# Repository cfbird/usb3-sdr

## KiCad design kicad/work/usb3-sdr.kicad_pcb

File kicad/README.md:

# usb3-sdr KiCad 9 project (Rev A0, generated)

Open `usb3-sdr.kicad_pro` in KiCad 9. Sheets: Power, RF front end, ADC and clock, USB 3 bridge, FPGA.

**Generated, not hand-drawn:** `gen/build.py` builds every sheet from `gen/design.py` (pin maps checked against
datasheets) and places a net label exactly on each pin end. Connectivity is exact; the visual layout is a packed
netlist style, not tidied. If you edit in KiCad, stop regenerating (or move the edits into design.py).

```
cd gen && python3 build.py && python3 verify.py && python3 check_lpf.py   # regenerate + check
kicad-cli sch erc --severity-all ../usb3-sdr.kicad_sch
```

## Verification status
| Check | Result |
|---|---|
| `gen/verify.py`: KiCad-exported netlist vs design.py | **203/203 nets identical** (no missing, merged or extra nets), 226 components |
| `gen/check_lpf.py`: gateware LPF → KiCad net → far-end **datasheet pin name** (through series resistors) | **71/71 signals land on the right pin**. Independent of design.py |
| ECP5 ball data: Lattice FPGA-SC-02033 CSV vs prjtrellis-db | Same 197 I/O balls, 0 bank mismatches, 0 clock-function mismatches. Pin names in the symbol are the official Lattice names |
| ERC | **2 violations, both expected**: J1 SSRX± "input not driven" (the host drives them through the cable) |
| Symbols vs datasheets | FT601Q (all 76 pins + EP), USB3 Micro-B, TPS62A02A, TLV75525, TPS7A20 DBV, TPS22918 (= TPS22917DBV pinout), W25Q128JVS, PHA-13LN, 74LVC1G17, G6K-2 vs HFD4/5-SR wiring |
| Footprints vs datasheets | FT601 QFN-76 EP 5.81×6.31 (DS Fig 8.3), AD9649 CP-32-11 EP 3.50 sq, BGA-256 14×14 0.8 mm, ADT4-6T+ CD637 |

## Open items
1. ~~ECP5 power/config unit~~ **Done** from Lattice FPGA-SC-02033 (`gen/ecp5_bg256.json`, extracted from the CSV).
   Configuration follows the Lattice ECP5 Versa board (FPGA-EB-02021 Fig. 12): CFG[2:0] = 010 (Master SPI) via 1k,
   10k pull-ups on PROGRAMN/INITN/DONE, 50 Ω series CCLK at the FPGA, JTAG powered from VCCIO8 (3.3 V).
   The 4.7k TCK pull-down is common Lattice practice, **not** taken from the Versa sheet.
2. J1 footprint is the stock Connfly DS1104-01, but the BOM lists Amphenol GSB343133HR. Pick one and match them.
3. GDT footprint is a 1812 placeholder until a GDT part is chosen.
4. FT601 data/control ball assignment follows the gateware LPF pool and is provisional; reorder at layout.

# PCB (stage 1: setup, placement, fan-out; not routed)
`gen/pcb_build.py` writes `usb3-sdr.kicad_pcb` from the exported netlist (footprints keep their symbol links, so
KiCad's *Update PCB from Schematic* works). It regenerates the placement from scratch, so after hand edits start, stop running it.

| Item | Setting |
|---|---|
| Board | 100 × 60 mm, 4 × M2.5 holes, 1.6 mm |
| Stackup | JLC04161H-7628: 35 µm / 0.2104 mm 7628 (εr 4.4) / 15 µm / 1.065 mm core / 15 µm / 0.2104 mm / 35 µm |
| Planes | In1 = solid GND. In2 = 1V1 under the BGA, 1V8_A under the ADC, 3V3_D across the digital half |
| Net classes | RF50 0.35 mm (confirm in the JLC calculator), USB90 diff 0.26 / 0.15, LVDS100 diff 0.20 / 0.15, PWR 0.4 mm, default 0.15 / 0.127 |
| Vias | 0.2 mm drill / 0.45 mm pad (JLC multilayer minimum, no surcharge) |
| BGA fan-out | 156 dog-bone vias: every power/GND ball, and signal balls in rings ≥ 2. Rings 0-1 escape on F.Cu between balls (needs ~0.1 mm neck-down) |

Checks (`kicad-cli pcb drc --schematic-parity`): **0 parity issues** (227 footprints = netlist, + 4 board-only holes).
Errors: only the 10 SMA edge-launch pads meeting Edge.Cuts (inherent to edge launch). Expected while unrouted: 499
unconnected, 112 dangling fan-out vias, 1V8_A plane isolated. Silkscreen overlap warnings are cosmetic (packed reference designators).

## PCB open items
1. **RF chain needs hand placement** in a straight line (SMA → GDT/clamp → K1/pad → LPF1 → notch → K2/LNA → LPF2 → T1 → ADC)
   with 50 Ω lines and the shield-can outlines. The generator only clusters it.
2. SMA edge position: set at the F.Fab flange line (+2.54 mm). **Check against the Amphenol 132289 drawing.**
3. FPGA 100 nF decoupling is on top around the BGA; moving it under the BGA (B.Cu, between vias) is better.
4. FT601 data balls: reorder to match the FT601 pin order at routing, then update the LPF + design.py and rerun verify/check_lpf.
5. 2V5 and 1V8_D BGA vias (VCCAUX, VCCIO7) need B.Cu feeds; the In2 split only covers 1V1 / 3V3_D / 1V8_A.

# PCB stage 2: scripted critical layout (gen/rf_layout.py), ready for DeepPCB
`gen/make_all.sh` runs everything: schematic → verify → check_lpf → ERC → netlist → PCB → DRC.

**RF chain**, a serpentine in the left third of the board (rows at y = 13 / 30 / 41 mm):
- Row A (→): SMA → GDT (Bourns 2038) → BAV99 clamp → K1 (bypass on NC above, 20 dB π-pad on NO below) → LPF1 → FM notch.
- Row B (←): K2 (bypass on NC below, LNA loop on NO above: DC block → PHA-13LN+ → choke/DC block → 3 dB pad) → LPF2.
- Row C (→): ADT4-6T+ → 200 Ω termination → 33 Ω → 10 pF kickback caps → AD9649 VIN±.
- Series parts sit in line, tank caps directly above their inductors, every shunt part has its own GND via to In1.
  Relays are rotated so COM3/COM6 sit in line with the row. All of it is locked.
**USB3 SuperSpeed**: FT601 → J1, one vertical jog per line (topmost line first, so nothing crosses), TX AC caps
on the lines, 0.2 mm width beside the 0.4 mm-pitch QFN. Locked.

Status: DRC errors only the inherent SMA edge items; schematic parity 0; every scripted net complete; 479 airwires left.
In1/In2 are marked as power layers, so signals stay on F.Cu/B.Cu. USB 2 pair renamed USB_D_P/N so diff-pair detection works.

**DeepPCB**: upload `deeppcb/usb3-sdr_for_deeppcb.zip` (or the two files) at app.deeppcb.ai (the KiCad plugin needs KiCad 10).
Check on return: (1) locked RF/USB tracks unchanged, (2) nothing routed on In1/In2, (3) USB90/LVDS100 pairs coupled,
(4) rerun `kicad-cli pcb drc --schematic-parity`. Their docs don't say whether locked tracks are honoured, so
diff the returned board against this one before accepting.

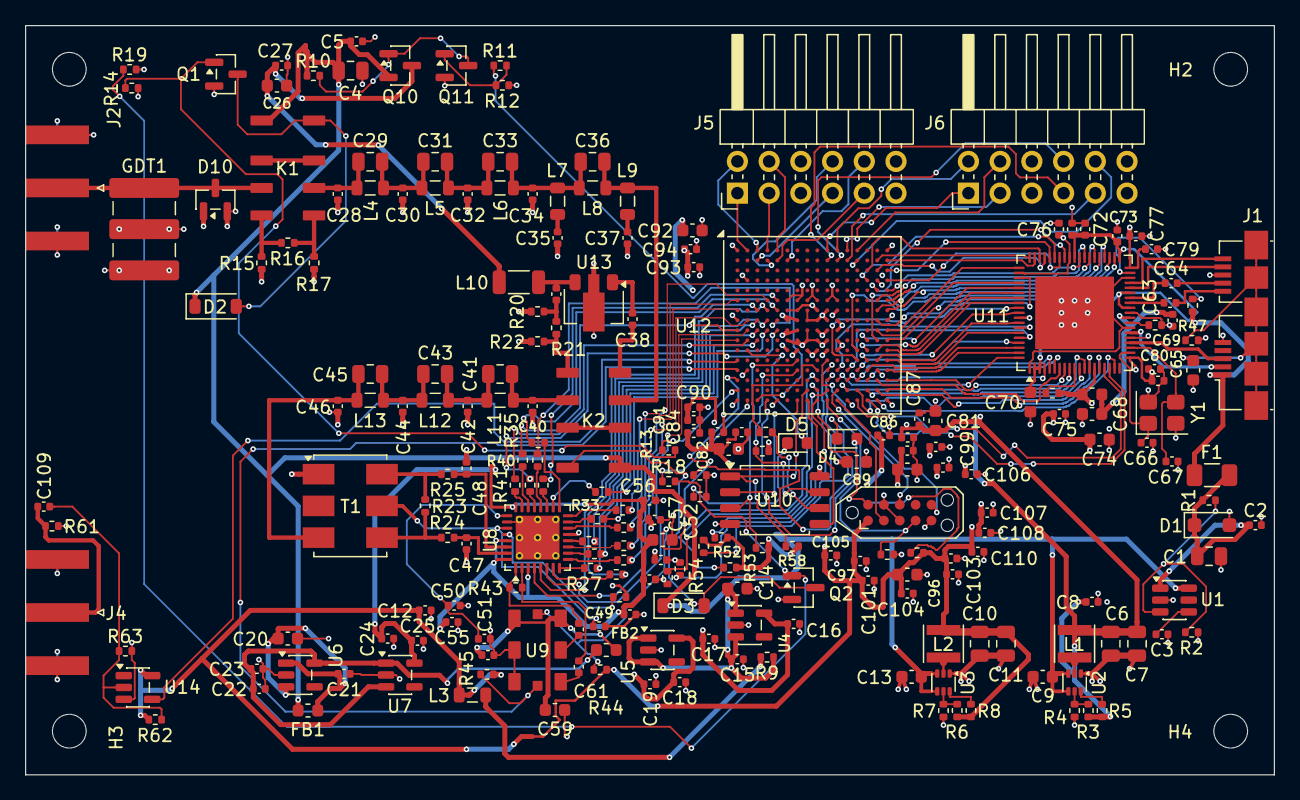
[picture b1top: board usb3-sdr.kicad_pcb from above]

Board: 4 copper layers, 100.0 x 60.0 mm, 231 parts (0 on the bottom side), 203 nets.

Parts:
C1, C4, C6, C7, C10, C11: 22u; C_0805_2012Metric
C2, C5, C8, C12, C17, C19, C21, C23, C25, C27, C38, C39, C49, C51, C53, C54, C55, C56, C58, C60, C61, C62, C63, C64, C69, C71, C72, C73, C75, C76, C77, C78, C79, C80, C83, C84, C85, C86, C87, C88, C90, C91, C93, C94, C97, C98, C99, C100, C101, C102, C103, C104, C105, C106, C107, C108, C109, C110: 100n; C_0402_1005Metric
C3: 1n; C_0402_1005Metric
C9, C13, C14, C20, C26, C52, C59, C74, C81, C82, C89, C92, C95, C96: 10u; C_0603_1608Metric
C15, C16, C18, C22, C24, C50, C57: 1u; C_0402_1005Metric
C28, C40: 62p C0G 2%; C_0402_1005Metric
C29, C41: 62p C0G 2%; C_0805_2012Metric
C30, C42: 130p C0G 2%; C_0402_1005Metric
C31, C43: 30p C0G 2%; C_0805_2012Metric
C32, C44: 160p C0G 2%; C_0402_1005Metric
C33, C45: 11p C0G 2%; C_0805_2012Metric
C34, C46: 91p C0G 2%; C_0402_1005Metric
C35: 39p C0G 2%; C_0402_1005Metric
C36: 15p C0G 2%; C_0805_2012Metric
C37: 47p C0G 2%; C_0402_1005Metric
C47, C48: 10p C0G; C_0402_1005Metric
C65: 4.7n 250V; C_0603_1608Metric
C66, C67: 33p C0G; C_0402_1005Metric
C68, C70: 4.7u; C_0603_1608Metric
D1: SMF5.0A; D_SOD-123F
D2, D3: 1N4148W; D_SOD-123
D4, D5: LED green; LED_0603_1608Metric
D10: BAV99; SOT-23
F1: 1.1A; Fuse_1206_3216Metric
FB1, FB2, FB3: 600R@100MHz; L_0603_1608Metric
GDT1: 2038-09-SM (90V); GDT_Bourns_2038
H1, H2, H3, H4: MountingHole_2.7mm_M2.5
J1: USB3 Micro-B; USB3_Micro-B_Connfly_DS1104-01
J2: SMA RF IN; SMA_Amphenol_132289_EdgeMount
J3: TC2050 JTAG; Tag-Connect_TC2050-IDC-NL_2x05_P1.27mm_Vertical
J4: SMA 10MHz REF; SMA_Amphenol_132289_EdgeMount
J5: PMOD0; PinHeader_2x06_P2.54mm_Horizontal
J6: PMOD1; PinHeader_2x06_P2.54mm_Horizontal
K1, K2: HFD4/5-SR; Relay_DPDT_Hongfa_HFD4-SR
L1, L2: 1u 2A shielded; L_Taiyo-Yuden_NR-30xx
L3: 1u; L_0805_2012Metric
L4, L8, L11: 180n 0805HP 2%; L_0805_2012Metric
L5, L6, L12, L13: 270n 0805HP 2%; L_0805_2012Metric
L7: 82n 0805HP 2%; L_0805_2012Metric
L9: 47n 0805HP 2%; L_0805_2012Metric
L10: 15u bias choke; L_1206_3216Metric
Q1, Q2, Q11: 2N7002; SOT-23
Q10: AO3401A; SOT-23
R1, R2, R5, R8, R10, R12, R14, R19: 100k; R_0402_1005Metric
R3: 100k 1%; R_0402_1005Metric
R4: 120k 1%; R_0402_1005Metric
R6: 226k 1%; R_0402_1005Metric
R7: 49.9k 1%; R_0402_1005Metric
R9: 0.47; R_0402_1005Metric
R11, R13, R18, R43: 100; R_0402_1005Metric
R15, R17: 61.9 1%; R_0402_1005Metric
R16: 249 1%; R_0402_1005Metric
R20, R22: 294 1%; R_0402_1005Metric
R21: 17.8 1%; R_0402_1005Metric
R23: 200 1%; R_0402_1005Metric
R24, R25: 33; R_0402_1005Metric
R26, R27, R28, R29, R30, R31, R32, R33, R34, R35, R36, R37, R38, R39, R40, R41: 22; R_0402_1005Metric
R42: 10k 1%; R_0402_1005Metric
R44, R45, R57, R58: 4.7k; R_0402_1005Metric
R46: 1M; R_0402_1005Metric
R47, R54, R55, R56: 1k; R_0402_1005Metric
R48: 1.6k 1%; R_0402_1005Metric
R49, R51, R52, R53, R59, R60, R62, R63: 10k; R_0402_1005Metric
R50: 50 (place at FPGA); R_0402_1005Metric
R61: 49.9; R_0402_1005Metric
R64, R65: 330; R_0402_1005Metric
T1: ADT4-6T+; Mini-Circuits_CD637_H5.23mm
U1: TPS22918DBVR; SOT-23-6
U2: TPS62A02ADRLR; SOT-563
U3: TPS62A02ADRLR (forced PWM); SOT-563
U4: TLV75525PDBVR; SOT-23-5
U5, U7: TPS7A2018PDBVR; SOT-23-5
U6: TPS7A2033PDBVR; SOT-23-5
U8: AD9649BCPZ-80; LFCSP-32-1EP_5x5mm_P0.5mm_EP3.5x3.5mm_ThermalVias
U9: LMK61E2-100M00SIAR; TI_SIA0008B_QFM-8_7x5mm
U10: W25Q128JVSIQ; SOIC-8_5.3x5.3mm_P1.27mm
U11: FT601Q-B-T; QFN-76-1EP_9x9mm_P0.4mm_EP5.81x6.31mm
U12: LFE5U-25F-6BG256C; BGA-256_14.0x14.0mm_Layout16x16_P0.8mm_Ball0.45mm_Pad0.32mm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
U13: PHA-13LN+; SOT-89-3
U14: 74LVC1G17; SOT-23-5
Y1: 30MHz 20pF X322530MSB4SI; Crystal_SMD_3225-4Pin_3.2x2.5mm

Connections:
1V1: C6.1, C7.1, C8.1, C81.1, C82.1, C83.1, C84.1, C85.1, C86.1, C87.1, C88.1, L1.2, R3.1, R5.2, U12.G6, U12.G7, U12.G9, U12.L8, U12.L9, U12.L10
1V8_A: C24.1, C25.1, C52.1, C53.1, C54.1, C55.1, C56.1, U7.5, U8.3, U8.24, U8.29, U8.32
1V8_D: C18.1, C19.1, C57.1, C58.1, C92.1, C93.1, C94.1, U5.5, U8.13, U12.H6, U12.H7
2V5: C16.1, C17.1, C89.1, C90.1, C91.1, U4.5, U12.G11, U12.L7
3V3_A: C22.1, C23.1, FB2.1, U6.5, U7.1, U7.3
3V3_D: C10.1, C11.1, C12.1, C74.1, C75.1, C76.1, C77.1, C78.1, C79.1, C80.1, C95.1, C96.1, C97.1, C98.1, C99.1, C100.1, C101.1, C102.1, C103.1, C104.1, C105.1, C106.1, C107.1, C108.1, C110.1, FB3.1, J3.1, J5.6, J5.12, J6.6, J6.12, L2.2, L3.1, R6.1, R8.2, R44.2, R45.2, R49.2, R51.2, R52.2, R53.2, R55.2, R58.2, R59.2, R60.2, R62.1, U10.8, U11.14, U11.20, U11.24, U11.38, U11.49, U11.59, U11.68, U12.F6, U12.F7, U12.F10, U12.F11, U12.H11, U12.J6, U12.J7, U12.J11, U12.K11, U12.L6, U12.L11, U14.5
5V_LNA: C26.1, C27.1, L10.1, Q10.3
5V_SW: C4.1, C5.1, C9.1, C13.1, D2.1, D3.1, FB1.1, K1.1, K2.1, Q10.2, R10.1, U1.6, U2.3, U2.4, U3.3, U3.4
/ADC and clock/3V3_CLK: C59.1, C60.1, FB2.2, U9.1, U9.6
/ADC and clock/ADC_CLKN: C61.2, R43.2, U8.2
/ADC and clock/ADC_CLKP: C62.2, R43.1, U8.1
/ADC and clock/ADC_D0_R: R26.1, U8.7
/ADC and clock/ADC_D1_R: R27.1, U8.8
/ADC and clock/ADC_D2_R: R28.1, U8.9
/ADC and clock/ADC_D3_R: R29.1, U8.10
/ADC and clock/ADC_D4_R: R30.1, U8.11
/ADC and clock/ADC_D5_R: R31.1, U8.12
/ADC and clock/ADC_D6_R: R32.1, U8.14
/ADC and clock/ADC_D7_R: R33.1, U8.15
/ADC and clock/ADC_D8_R: R34.1, U8.16
/ADC and clock/ADC_D9_R: R35.1, U8.17
/ADC and clock/ADC_D10_R: R36.1, U8.18
/ADC and clock/ADC_D11_R: R37.1, U8.19
/ADC and clock/ADC_D12_R: R38.1, U8.20
/ADC and clock/ADC_D13_R: R39.1, U8.21
/ADC and clock/ADC_DCO_R: R40.1, U8.22
/ADC and clock/ADC_OR_R: R41.1, U8.23
/ADC and clock/ADC_RBIAS: R42.1, U8.28
/ADC and clock/ADC_VREF: C50.1, C51.1, U8.25
/ADC and clock/LMK_OUTN: C62.1, U9.5
/ADC and clock/LMK_OUTP: C61.1, U9.4
/FPGA/CCLK_FPGA: R50.1, U12.N9
/FPGA/D4_K: D4.1, R64.1
/FPGA/D5_K: D5.1, R65.1
/FPGA/FLASH_CS_N: R58.1, U10.1, U12.R8
/FPGA/FLASH_IO0: U10.5, U12.T8
/FPGA/FLASH_IO1: U10.2, U12.T7
/FPGA/FLASH_IO2: R59.1, U10.3, U12.M7
/FPGA/FLASH_IO3: R60.1, U10.7, U12.N7
/FPGA/FPGA_CCLK: R50.2, U10.6
/FPGA/FPGA_CFG0: R54.1, U12.N10
/FPGA/FPGA_CFG1: R55.1, U12.P10
/FPGA/FPGA_CFG2: R56.1, U12.R10
/FPGA/FPGA_DONE: R53.1, U12.P9
/FPGA/FPGA_INIT_N: R52.1, U12.T9
/FPGA/FPGA_PROGRAM_N: J3.10, R51.1, U12.R9
/FPGA/FPGA_TCK: J3.4, R57.1, U12.T10
/FPGA/FPGA_TDI: J3.8, U12.R11
/FPGA/FPGA_TDO: J3.6, U12.M10
/FPGA/FPGA_TMS: J3.2, U12.T11
/FPGA/LED0: D4.2, U12.T4
/FPGA/LED1: D5.2, U12.L2
/FPGA/PMOD0_0: J5.1, U12.A2
/FPGA/PMOD0_1: J5.2, U12.A3
/FPGA/PMOD0_2: J5.3, U12.A4
/FPGA/PMOD0_3: J5.4, U12.A5
/FPGA/PMOD0_4: J5.7, U12.B3
/FPGA/PMOD0_5: J5.8, U12.B4
/FPGA/PMOD0_6: J5.9, U12.B5
/FPGA/PMOD0_7: J5.10, U12.B6
/FPGA/PMOD1_0: J6.1, U12.A10
/FPGA/PMOD1_1: J6.2, U12.A11
/FPGA/PMOD1_2: J6.3, U12.A12
/FPGA/PMOD1_3: J6.4, U12.A13
/FPGA/PMOD1_4: J6.7, U12.B10
/FPGA/PMOD1_5: J6.8, U12.B11
/FPGA/PMOD1_6: J6.9, U12.B12
/FPGA/PMOD1_7: J6.10, U12.B13
/FPGA/REF10M: U12.M1, U14.4
/FPGA/REF_AC: C109.2, R62.2, R63.1, U14.2
/FPGA/REF_IN: C109.1, J4.1, R61.1
/Power/3V3_D_F: C14.1, C15.1, R9.2, U4.1, U4.3, U5.1, U5.3
/Power/3V3_PF: L3.2, R9.1
/Power/5V_A: C20.1, C21.1, FB1.2, U6.1, U6.3
/Power/FB_1V1: R3.2, R4.1, U2.5
/Power/FB_3V3: R6.2, R7.1, U3.5
/Power/LS_CT: C3.1, U1.4
/Power/LS_ON: R1.2, R2.1, U1.3
/Power/PG_1V1: R5.1, U2.6
/Power/PG_3V3: R8.1, U3.6
/Power/Q10_G: Q10.1, Q11.3, R10.2
/Power/Q11_G: Q11.1, R11.2, R12.1
/Power/SW_1V1: L1.1, U2.2
/Power/SW_3V3: L2.1, U3.2
/Power/VBUS_F: C1.1, C2.1, D1.1, F1.2, R1.1, U1.1
/RF front end/AIN_N_T: R23.2, R25.1, T1.6
/RF front end/AIN_P_T: R23.1, R24.1, T1.4
/RF front end/K1_COIL: D2.2, K1.8, Q1.3
/RF front end/K2_COIL: D3.2, K2.8, Q2.3
/RF front end/LNA_BYP: K2.2, K2.7
/RF front end/LNA_IN: C38.1, K2.4
/RF front end/LNA_O: C39.2, R20.1, R21.1
/RF front end/LNA_PAD_OUT: K2.5, R21.2, R22.1
/RF front end/LNA_RFIN: C38.2, U13.1
/RF front end/LNA_RFOUT: C39.1, L10.2, U13.3
/RF front end/LPF1_N2: C29.2, C30.1, C31.1, L4.2, L5.1
/RF front end/LPF1_N4: C31.2, C32.1, C33.1, L5.2, L6.1
/RF front end/LPF1_OUT: C33.2, C34.1, C36.1, L6.2, L7.1, L8.1
/RF front end/LPF2_IN: C40.1, C41.1, K2.6, L11.1
/RF front end/LPF2_N2: C41.2, C42.1, C43.1, L11.2, L12.1
/RF front end/LPF2_N4: C43.2, C44.1, C45.1, L12.2, L13.1
/RF front end/LPF2_OUT: C45.2, C46.1, L13.2, T1.3
/RF front end/NOTCH_OUT: C36.2, K2.3, L8.2, L9.1
/RF front end/PAD_BYP: K1.2, K1.7
/RF front end/PAD_IN: K1.4, R15.1, R16.1
/RF front end/PAD_OUT: K1.5, R16.2, R17.1
/RF front end/Q1_G: Q1.1, R13.2, R14.1
/RF front end/Q2_G: Q2.1, R18.2, R19.1
/RF front end/RF_A: C28.1, C29.1, K1.6, L4.1
/RF front end/RF_IN: D10.3, GDT1.1, J2.1, K1.3
/RF front end/TRAP1: C35.1, L7.2
/RF front end/TRAP3: C37.1, L9.2
/USB 3 bridge/FT_1V0: C70.1, C71.1, C72.1, C73.1, U11.2, U11.3, U11.30, U11.33, U11.39, U11.48
/USB 3 bridge/FT_RREF: R48.1, U11.27
/USB 3 bridge/FT_SIWU: R49.1, U11.10
/USB 3 bridge/FT_TXN: C63.1, U11.31
/USB 3 bridge/FT_TXP: C64.1, U11.32
/USB 3 bridge/FT_VBUS: R47.2, U11.37
/USB 3 bridge/FT_VDDA: C68.1, C69.1, FB3.2, U11.28
/USB 3 bridge/FT_XI: C66.1, U11.21, Y1.1
/USB 3 bridge/FT_XO: C67.1, U11.22, Y1.3
/USB 3 bridge/USB_D_N: J1.2, U11.25
/USB 3 bridge/USB_D_P: J1.3, U11.23
/USB 3 bridge/USB_SHIELD: C65.1, J1.11, R46.1
/USB 3 bridge/USB_SSRXN: J1.9, U11.34
/USB 3 bridge/USB_SSRXP: J1.10, U11.35
/USB 3 bridge/USB_SSTXN: C63.2, J1.6
/USB 3 bridge/USB_SSTXP: C64.2, J1.7
ADC_CSB: U8.4, U12.H2
ADC_D0: R26.2, U12.G4
ADC_D1: R27.2, U12.H3
ADC_D2: R28.2, U12.F4
ADC_D3: R29.2, U12.J3
ADC_D4: R30.2, U12.J2
ADC_D5: R31.2, U12.H4
ADC_D6: R32.2, U12.F1
ADC_D7: R33.2, U12.K3
ADC_D8: R34.2, U12.G1
ADC_D9: R35.2, U12.G5
ADC_D10: R36.2, U12.J4
ADC_D11: R37.2, U12.F5
ADC_D12: R38.2, U12.H5
ADC_D13: R39.2, U12.J5
ADC_DCO: R40.2, U12.J1
ADC_OR: R41.2, U12.K2
ADC_SCLK: U8.5, U12.G3
ADC_SDIO: U8.6, U12.K1
ADC_VCM: C49.1, T1.5, U8.27
ADC_VINN: C48.1, R25.2, U8.30
ADC_VINP: C47.1, R24.2, U8.31
FT_BE0: U11.4, U12.P12
FT_BE1: U11.5, U12.P13
FT_BE2: U11.6, U12.P14
FT_BE3: U11.7, U12.P15
FT_CLK: U11.58, U12.J16
FT_D0: U11.40, U12.K16
FT_D1: U11.41, U12.L13
FT_D2: U11.42, U12.K15
FT_D3: U11.43, U12.G16
FT_D4: U11.44, U12.G15
FT_D5: U11.45, U12.F16
FT_D6: U11.46, U12.F15
FT_D7: U11.47, U12.E16
FT_D8: U11.50, U12.E15
FT_D9: U11.51, U12.D16
FT_D10: U11.52, U12.D14
FT_D11: U11.53, U12.C16
FT_D12: U11.54, U12.C15
FT_D13: U11.55, U12.C14
FT_D14: U11.56, U12.B16
FT_D15: U11.57, U12.B15
FT_D16: U11.60, U12.H15
FT_D17: U11.61, U12.J15
FT_D18: U11.62, U12.K14
FT_D19: U11.63, U12.L14
FT_D20: U11.64, U12.L15
FT_D21: U11.65, U12.L16
FT_D22: U11.66, U12.M13
FT_D23: U11.67, U12.M14
FT_D24: U11.69, U12.M15
FT_D25: U11.70, U12.N11
FT_D26: U11.71, U12.M16
FT_D27: U11.72, U12.N12
FT_D28: U11.73, U12.N13
FT_D29: U11.74, U12.N14
FT_D30: U11.75, U12.N16
FT_D31: U11.76, U12.P11
FT_GPIO0: U11.17, U12.T14
FT_GPIO1: U11.18, U12.T15
FT_OE_N: U11.13, U12.R15
FT_RD_N: U11.12, U12.R14
FT_RESET_N: U11.15, U12.R16
FT_RXF_N: U11.9, U12.R12
FT_TXE_N: U11.8, U12.P16
FT_WAKEUP_N: U11.16, U12.T13
FT_WR_N: U11.11, U12.R13
GND: C1.2, C2.2, C3.2, C4.2, C5.2, C6.2, C7.2, C8.2, C9.2, C10.2, C11.2, C12.2, C13.2, C14.2, C15.2, C16.2, C17.2, C18.2, C19.2, C20.2, C21.2, C22.2, C23.2, C24.2, C25.2, C26.2, C27.2, C28.2, C30.2, C32.2, C34.2, C35.2, C37.2, C40.2, C42.2, C44.2, C46.2, C47.2, C48.2, C49.2, C50.2, C51.2, C52.2, C53.2, C54.2, C55.2, C56.2, C57.2, C58.2, C59.2, C60.2, C65.2, C66.2, C67.2, C68.2, C69.2, C70.2, C71.2, C72.2, C73.2, C74.2, C75.2, C76.2, C77.2, C78.2, C79.2, C80.2, C81.2, C82.2, C83.2, C84.2, C85.2, C86.2, C87.2, C88.2, C89.2, C90.2, C91.2, C92.2, C93.2, C94.2, C95.2, C96.2, C97.2, C98.2, C99.2, C100.2, C101.2, C102.2, C103.2, C104.2, C105.2, C106.2, C107.2, C108.2, C110.2, D1.2, D10.1, D10.2, GDT1.2, GDT1.3, J1.5, J1.8, J2.2, J3.3, J3.5, J3.9, J4.2, J5.5, J5.11, J6.5, J6.11, Q1.2, Q2.2, Q11.2, R2.2, R4.2, R7.2, R12.2, R14.2, R15.2, R17.2, R19.2, R20.2, R22.2, R42.2, R46.2, R48.2, R54.2, R56.2, R57.2, R61.2, R63.2, R64.2, R65.2, T1.1, U1.2, U2.1, U3.1, U4.2, U5.2, U6.2, U7.2, U8.26, U8.33, U9.2, U9.3, U10.4, U11.1, U11.26, U11.29, U11.36, U11.77, U12.A1, U12.A16, U12.D2, U12.D15, U12.F8, U12.F9, U12.G8, U12.G10, U12.H1, U12.H8, U12.H9, U12.H10, U12.H16, U12.J8, U12.J9, U12.J10, U12.K6, U12.K7, U12.K8, U12.K9, U12.K10, U12.N2, U12.N15, U12.T1, U12.T5, U12.T12, U12.T16, U13.2, U14.3, Y1.2, Y1.4
LMK_SCL: R45.1, U9.8, U12.N1
LMK_SDA: R44.1, U9.7, U12.P1
LNA_EN: R11.1, U12.T3
RLY_LNA: R18.1, U12.T2
RLY_PAD: R13.1, U12.R1
VBUS: F1.1, J1.1, R47.1

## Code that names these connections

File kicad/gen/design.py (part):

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        ("J2", "Connector:Conn_Coaxial", "SMA RF IN", "Connector_Coaxial:SMA_Amphenol_132289_EdgeMount",
         {"1": "RF_IN", "2": "GND"}, 1),
        # Bourns 2038-09-SM is 3-electrode: line 1, centre ground 2, line 3 also grounded -> single line-to-GND arrester
        ("GDT1", "Device:GDT_3Pin", "2038-09-SM (90V)", "Fuse:GDT_Bourns_2038", {"1": "RF_IN", "2": "GND", "3": "GND"}, 1),
        # antiparallel clamp: common node (pin 3) to the line, outer pins to GND
        ("D10", "Diode:BAV99", "BAV99", SOT23, {"3": "RF_IN", "1": "GND", "2": "GND"}, 1),
        # 20 dB pad relay: de-energised = through (NC)
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
def adc_clk():
    d = {str(p): f"ADC_D{i}_R" for i, p in enumerate([7, 8, 9, 10, 11, 12, 14, 15, 16, 17, 18, 19, 20, 21])}
    pins = {"31": "ADC_VINP", "30": "ADC_VINN", "27": "ADC_VCM", "25": "ADC_VREF", "26": "GND", "28": "ADC_RBIAS",
            "1": "ADC_CLKP", "2": "ADC_CLKN", "4": "ADC_CSB", "5": "ADC_SCLK", "6": "ADC_SDIO",
            "22": "ADC_DCO_R", "23": "ADC_OR_R", "3": "1V8_A", "24": "1V8_A", "29": "1V8_A", "32": "1V8_A",
            "13": "1V8_D", "33": "GND", **d}
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          "20": "3V3_D", "24": "3V3_D", "38": "3V3_D", "14": "3V3_D", "49": "3V3_D", "59": "3V3_D", "68": "3V3_D",
          "28": "FT_VDDA", "37": "FT_VBUS", "21": "FT_XI", "22": "FT_XO", "23": "USB_D_P", "25": "USB_D_N",
          "27": "FT_RREF", "31": "FT_TXN", "32": "FT_TXP", "34": "USB_SSRXN", "35": "USB_SSRXP",
          "10": "FT_SIWU", "19": "", "17": "FT_GPIO0", "18": "FT_GPIO1",
          "15": "FT_RESET_N", "16": "FT_WAKEUP_N", "8": "FT_TXE_N", "9": "FT_RXF_N", "11": "FT_WR_N",
          "12": "FT_RD_N", "13": "FT_OE_N", "58": "FT_CLK",
          "4": "FT_BE0", "5": "FT_BE1", "6": "FT_BE2", "7": "FT_BE3"}
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                net = {"adc_d": "ADC_D", "ft_data": "FT_D", "ft_be": "FT_BE"}[mm.group(1)] + mm.group(2)
            ball_net[ball] = net
    # FT601 GPIO0/1 go to the two spare FT-pool balls (provisional, like the rest of the FT map)
    ball_net.update({"P13": "FT_GPIO0", "P14": "FT_GPIO1"})
    # config flash on bank 8 (balls from prjtrellis function names): CSN R8, MOSI/D0 T8, MISO/D1 T7, D2 M7, D3 N7
    ball_net.update({"R8": "FLASH_CS_N", "T8": "FLASH_IO0", "T7": "FLASH_IO1", "M7": "FLASH_IO2", "N7": "FLASH_IO3"})
    # two PMODs on banks 0/1, outer rings
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
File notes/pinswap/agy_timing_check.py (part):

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FT_MIN_SKEW_MM = -10.0      # L_sig - L_CLK >= -10.0 mm (read/write hold slack >= +680 ps)
FT_MAX_SKEW_MM = 30.0       # L_sig - L_CLK <= +30.0 mm (longer data traces increase hold slack; setup slack > +1400 ps)
FT_MAX_TOTAL_MM = 45.0      # <= 45.0 mm (LVCMOS33 tau*L <= t_r/3 SI limit; L_crit = t_r/(2*tau) = 69.2 mm)
FT_ASYNC_MAX_MM = 60.0      # FT_RESET_N/WAKEUP_N/GPIO0/GPIO1 asynchronous per FT601Q Table 3.2 (exempt from FT_CLK skew)

# Net lists
ADC_DATA_NETS = [f"ADC_D{i}" for i in range(14)] + ["ADC_OR"]
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    + ["FT_TXE_N", "FT_RXF_N", "FT_WR_N", "FT_RD_N", "FT_OE_N", "FT_SIWU_N"]
)
FT_ALL_SYNC_NETS = ["FT_CLK"] + FT_SYNC_NETS
FT_ASYNC_NETS = ["FT_RESET_N", "FT_WAKEUP_N", "FT_GPIO0", "FT_GPIO1"]


# ==============================================================================
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                    f"{slacks['wr_setup_fab_ps']:>+10.0f} {status:>8}"
                )

        # Check asynchronous FT601 control/GPIO nets (exempt from FT_CLK skew per Table 3.2)
        for net in FT_ASYNC_NETS:
            val = get_len(net)
            if val is not None:
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        synth[ctrl] = 16.0 + idx * 1.2
    synth["FT_RESET_N"] = 28.09
    synth["FT_WAKEUP_N"] = 16.65
    synth["FT_GPIO0"] = 22.87
    synth["FT_GPIO1"] = 26.86

    return synth

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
